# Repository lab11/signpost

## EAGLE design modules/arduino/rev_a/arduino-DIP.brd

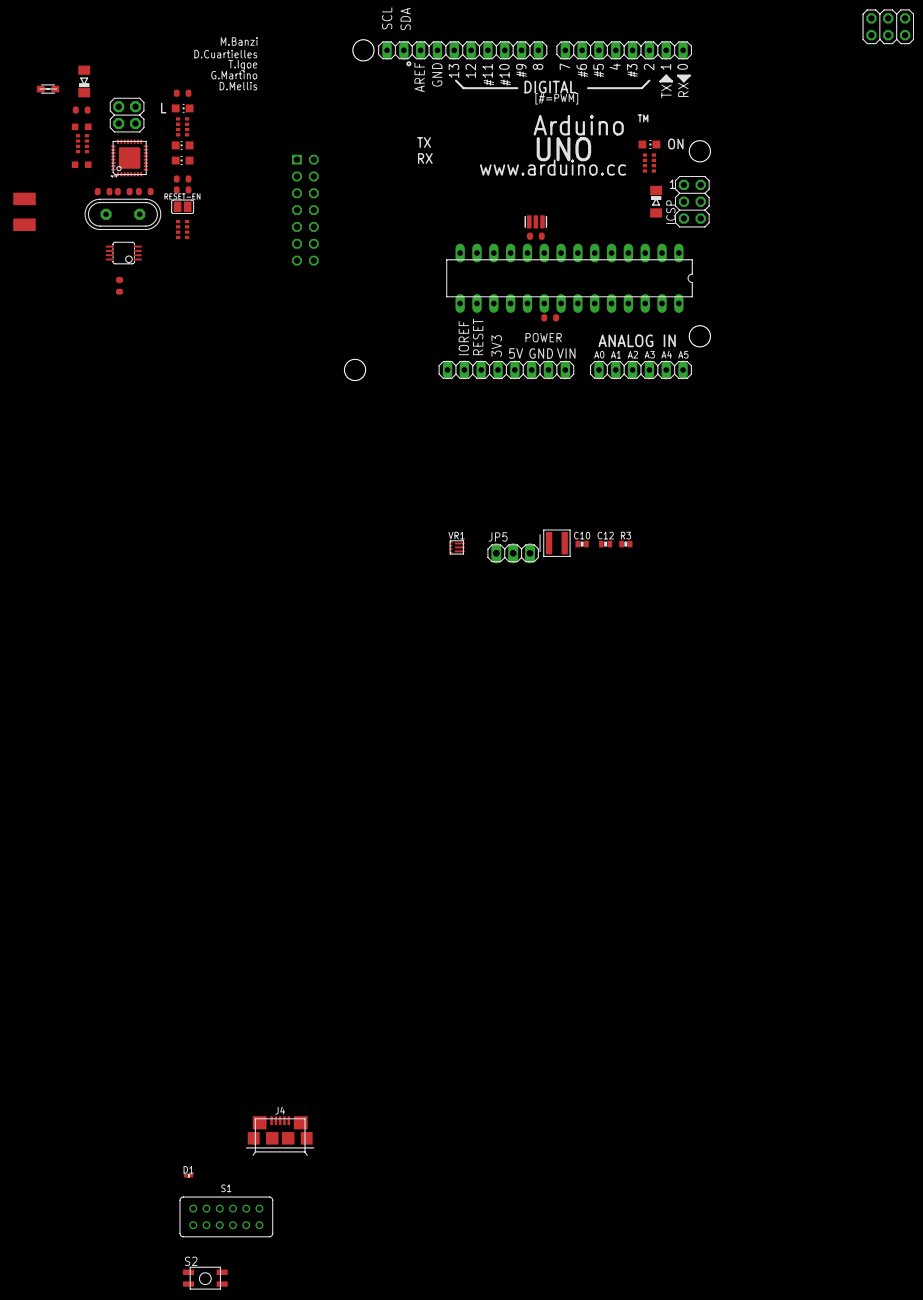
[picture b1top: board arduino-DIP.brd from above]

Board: 2 copper layers, 49 parts (1 on the bottom side), 67 nets, no tracks yet.

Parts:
AD: 6x1F-H8.5; 1X06
C1, C4, C5, C6, C7: 100n; C0603-ROUND
C8: 1u; C0603-ROUND
C9, C11: 22p; C0603-ROUND
C10: 10uF; 0603_CAP
C12: 22uF; 0603_CAP
D1: DIODE; 0402_DIODE
D2, D3: CD1206-S01575; MINIMELF
F1: MF-MSMF050-2 500mA; L1812
GROUND: SJ
ICSP, ICSP1: 3x2 M; 2X03
IOH: 10x1F-H8.5; 1X10
IOL: 8x1F-H8.5; 1X08
J1: MODULE_GENERIC
J4: MICRO_USB_B_HIROSE_ZX62-B-5PA(11); USB_MICRO_B-HIROSE-ZX62-B-5PA(11)
JP2: 2x2 M - NM; 2X02
JP5: 1X03
L: YELLOW; CHIP-LED0805
L1: BLM21; 0805
L2: 0.47uH; XFL4015
ON: GREEN; CHIP-LED0805
POWER: 8x1F-H8.5; 1X08
R1, R2: 1M; R0603-ROUND
R3: 1MΩ; 0603-RES
RESET-EN: SJ
RN1: 10K; CAY16
RN2, RN4: 1K; CAY16
RN3: 22R; CAY16
RX: YELLOW; CHIP-LED0805
S1: MFS401N-2-Z
S2: EVQP2
TX: YELLOW; CHIP-LED0805
U3: ATMEGA16U2-MU(R); MLF32
U5: LMV358IDGKR; MSOP08
VR1: TPS62086; RLT0007A
Y1: 16MHz; QS
Y2: CSTCE16M0V53-R0 16MHZ; RESONATOR
Z1, Z2: CG0603MLC-05E; CT/CN0603
ZU4: ATMEGA328P-PU; DIL28-3

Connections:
+3V3: C12.1, JP5.3, L2.2, POWER.4, R3.2, VR1.3, VR1.4
+5V: C1.2, C6.2, C7.1, D1.CATHODE, D2.C, D3.C, ICSP.2, ICSP1.2, POWER.2, POWER.5, RN1.3, RN1.5, RN2.2, RN2.3, RN4.3, RN4.4, U3.4, U3.32, U5.8, ZU4.7, ZU4.20
AD0: AD.1, ZU4.23
AD1: AD.2, ZU4.24
AD2: AD.3, ZU4.25
AD3: AD.4, ZU4.26
AD4/SDA: AD.5, IOH.9, ZU4.27
AD5/SCL: AD.6, IOH.10, ZU4.28
ARD_USB_D+: RN3.5, S1.8, Z1.1
ARD_USB_D-: RN3.8, S1.5, Z2.1
ARD_USB_GND: C8.2, GROUND.2, L1.1, S1.11, U3.28
ARD_USB_VBUS: D1.ANODE, F1.2, S1.2
AREF: C4.2, IOH.8, ZU4.21
DTR: C5.1, RN2.4, U3.13
EXT_USB_D+: J4.3, S1.9
EXT_USB_D-: J4.2, S1.6
EXT_USB_GND: J4.5, S1.12
EXT_USB_VBUS: J4.1, S1.3
GND: C1.1, C4.1, C6.1, C7.2, C9.2, C10.2, C11.2, C12.2, GROUND.1, ICSP.6, ICSP1.6, IOH.7, J1.1, J1.14, L.C, ON.C, POWER.6, POWER.7, RN2.5, S1.10, S2.P$1, S2.P$3, U3.3, U3.33, U5.4, VR1.5, Y2.2, ZU4.8, ZU4.22
IO0: IOL.1, RN4.2, ZU4.2
IO1: IOL.2, RN4.1, ZU4.3
IO2: IOL.3, ZU4.4
IO3: IOL.4, ZU4.5
IO4: IOL.5, ZU4.6
IO5: IOL.6, ZU4.11
IO6: IOL.7, ZU4.12
IO7: IOL.8, ZU4.13
IO8: IOH.1, ZU4.14
IO9: IOH.2, ZU4.15
L13: RN2.8, U5.6, U5.7
M8RXD: RN4.7, U3.9
M8TXD: RN4.8, U3.8
MISO: ICSP.1, IOH.5, ZU4.18
MISO2: ICSP1.1, U3.17
MOD_5V: C10.1, J1.2, JP5.1, VR1.1, VR1.7
MOD_USB_D+: J1.11, S1.7
MOD_USB_D-: J1.12, S1.4
MOD_USB_VBUS: J1.13, S1.1
MOD_VCCIO: J1.4, JP5.2
MOSI: ICSP.4, IOH.4, ZU4.17
MOSI2: ICSP1.4, U3.16
unnamed: L.A, RN2.1
unnamed: L2.1, VR1.6
unnamed: ON.A, RN4.5, RN4.6
unnamed: RN2.7, RX.A
unnamed: RN2.6, TX.A
PB4: JP2.1, U3.18
PB5: JP2.3, U3.19
PB6: JP2.2, U3.20
PB7: JP2.4, U3.21
POWER_GOOD: R3.1, VR1.2
RD+: RN3.4, U3.29
RD-: RN3.1, U3.30
RESET: C5.2, D2.A, ICSP.5, POWER.3, RESET-EN.1, RESET-EN.2, RN1.4, S2.P$2, S2.P$4, ZU4.1
RESET2: D3.A, ICSP1.5, RN1.6, U3.24
RXLED: RX.C, U3.10
SCK: ICSP.3, IOH.6, U5.5, ZU4.19
SCK2: ICSP1.3, U3.15
SS: IOH.3, ZU4.16
TP_VUCAP: C8.1, U3.27
TXLED: TX.C, U3.11
USBVCC: F1.1, U3.31
USHIELD: L1.2, Z1.2, Z2.2
XT1: C9.1, R1.1, U3.1, Y1.2
XT2: C11.1, R1.2, U3.2, Y1.1
XTAL1: R2.1, Y2.3, ZU4.9
XTAL2: R2.2, Y2.1, ZU4.10

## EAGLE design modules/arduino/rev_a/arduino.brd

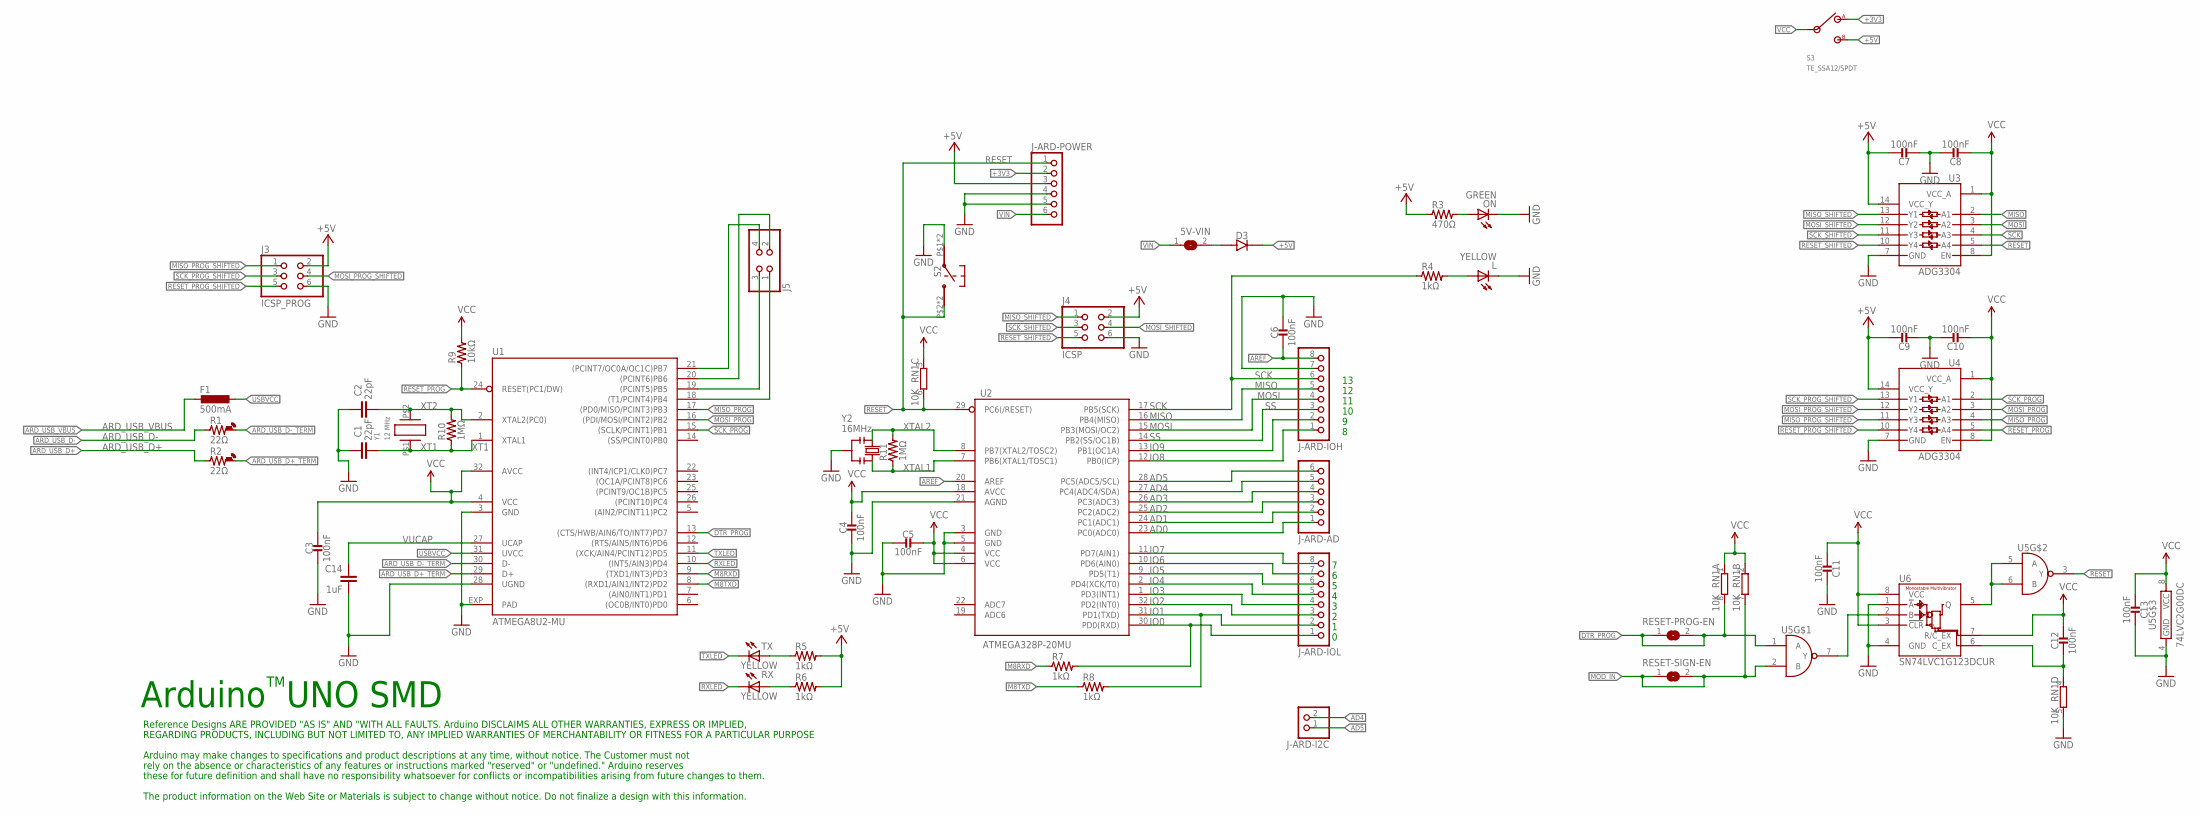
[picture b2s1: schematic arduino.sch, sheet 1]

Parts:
5V-VIN: SJ
C1, C2: 22pF; C0603-ROUND
C3, C4, C5, C6, C7, C8, C9, C10, C11, C12, C13: 100nF; 0603_CAP
C14: 1uF; C0603-ROUND
D3: DIODE; 0402_DIODE; DIGIKEY P18981CT-ND
F1: 500mA; L1812; DIGIKEY MF-MSMF050-2CT-ND
J3: ICSP_PROG; 2X03
J4: ICSP; 2X03
J5: PINHD-2X2; 2X02
J-ARD-AD: PINHD-1X6; 1X06
J-ARD-I2C: PINHD-1X2; 1X02
J-ARD-IOH: PINHD-1X8; 1X08
J-ARD-IOL: PINHD-1X8; 1X08
J-ARD-POWER: PINHD-1X6; 1X06
L: YELLOW; CHIP-LED0805
ON: GREEN; CHIP-LED0805
R1, R2: 22Ω; 0402_RES-HIGH_SPEED
R3: 470Ω; 0603-RES
R4, R5, R6, R7, R8: 1kΩ; 0603-RES
R9: 10kΩ; 0603-RES
R10, R11: 1MΩ; 0603-RES
RESET-PROG-EN: SJ
RESET-SIGN-EN: SJ
RN1: 10K; CAY16; DIGIKEY CAY16-103J4GLFCT-ND
RX: YELLOW; CHIP-LED0805
S2: EVQP2
S3: TE_SSA12/SPDT
TX: YELLOW; CHIP-LED0805
U1: ATMEGA8U2-MU; QFN32; DIGIKEY ATMEGA8U2-MURCT-ND
U2: ATMEGA328P-20MU; MLF32; DIGIKEY ATMEGA328P-MU-ND
U3, U4: ADG3304; TSSOP-14/5MM
U5: 74LVC2G00DC; VSSOP-8
U6: SN74LVC1G123DCUR; VFSOP-8
Y1: 12 MHz; ABM3; DIGIKEY 535-9103-1-ND
Y2: 16MHz; RESONATOR; DIGIKEY 490-1198-1-ND

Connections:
+3V3: J-ARD-POWER.2, S3.1 (A); also elsewhere on the board
+5V: C7.1, C9.1, D3.CATHODE, J3.2, J4.2, J-ARD-POWER.3, R3.1, R5.2, R6.2, S3.2 (B), U3.14 (VCC_Y), U4.14 (VCC_Y); also elsewhere on the board
AD0: J-ARD-AD.1, U2.23 (PC0(ADC0))
AD1: J-ARD-AD.2, U2.24 (PC1(ADC1))
AD2: J-ARD-AD.3, U2.25 (PC2(ADC2))
AD3: J-ARD-AD.4, U2.26 (PC3(ADC3))
AD4: J-ARD-AD.5, J-ARD-I2C.2, U2.27 (PC4(ADC4/SDA))
AD5: J-ARD-AD.6, J-ARD-I2C.1, U2.28 (PC5(ADC5/SCL))
ARD_USB_D+: R2.2; also elsewhere on the board
ARD_USB_D+_TERM: R2.1, U1.29 (D+)
ARD_USB_D-: R1.2; also elsewhere on the board
ARD_USB_D-_TERM: R1.1, U1.30 (D-)
ARD_USB_VBUS: F1.2; also elsewhere on the board
AREF: C6.2, J-ARD-IOH.8, U2.20 (AREF)
DTR_PROG: RESET-PROG-EN.1, RESET-PROG-EN.2, RN1.8 (2), U1.13 ((CTS/HWB/AIN6/TO/INT7)PD7), U5.1 (A)
GND: C1.2, C2.2, C3.2, C4.2, C5.2, C6.1, C7.2, C8.1, C9.2, C10.1, C11.1, C13.1, C14.2, J3.6, J4.6, J-ARD-IOH.7, J-ARD-POWER.4, J-ARD-POWER.5, L.C, ON.C, RN1.5 (2), S2.P$1, S2.P$3, U1.3 (GND), U1.28 (UGND), U1.EXP (PAD), U2.3 (GND), U2.5 (GND), U2.21 (AGND), U3.7 (GND), U4.7 (GND), U5.4 (GND), U6.1 (!A), U6.4 (GND), Y2.2; also elsewhere on the board
IO0: J-ARD-IOL.1, R7.2, U2.30 (PD0(RXD))
IO1: J-ARD-IOL.2, R8.2, U2.31 (PD1(TXD))
IO2: J-ARD-IOL.3, U2.32 (PD2(INT0))
IO3: J-ARD-IOL.4, U2.1 (PD3(INT1))
IO4: J-ARD-IOL.5, U2.2 (PD4(XCK/T0))
IO5: J-ARD-IOL.6, U2.9 (PD5(T1))
IO6: J-ARD-IOL.7, U2.10 (PD6(AIN0))
IO7: J-ARD-IOL.8, U2.11 (PD7(AIN1))
IO8: J-ARD-IOH.1, U2.12 (PB0(ICP))
IO9: J-ARD-IOH.2, U2.13 (PB1(OC1A))
M8RXD: R7.1, U1.9 ((TXD1/INT3)PD3)
M8TXD: R8.1, U1.8 ((RXD1/AIN1/INT2)PD2)
MISO: J-ARD-IOH.5, U2.16 (PB4(MISO)), U3.2 (A1)
MISO_PROG: U1.17 ((PD0/MISO/PCINT3)PB3), U4.4 (A3)
MISO_PROG_SHIFTED: J3.1, U4.11 (Y3)
MISO_SHIFTED: J4.1, U3.13 (Y1)
MOD_IN: RESET-SIGN-EN.1, RESET-SIGN-EN.2, RN1.7 (2), U5.2 (B); also elsewhere on the board
MOSI: J-ARD-IOH.4, U2.15 (PB3(MOSI/OC2)), U3.3 (A2)
MOSI_PROG: U1.16 ((PDI/MOSI/PCINT2)PB2), U4.3 (A2)
MOSI_PROG_SHIFTED: J3.4, U4.12 (Y2)
MOSI_SHIFTED: J4.4, U3.12 (Y2)
unnamed: L.A, R4.2
unnamed: J5.1, U1.18 ((T1/PCINT4)PB4)
unnamed: ON.A, R3.2
unnamed: J5.3, U1.19 ((PCINT5)PB5)
unnamed: J5.2, U1.20 ((PCINT6)PB6)
unnamed: J5.4, U1.21 ((PCINT7/OC0A/OC1C)PB7)
unnamed: C12.2, RN1.4 (1), U6.6 (C_EX)
unnamed: 5V-VIN.2, D3.ANODE
unnamed: U5.7 (Y), U6.2 (B)
unnamed: U5.5 (A), U5.6 (B), U6.5 (Q)
unnamed: R6.1, RX.A
unnamed: R5.1, TX.A
RESET: J-ARD-POWER.1, RN1.6 (2), S2.P$2, S2.P$4, U2.29 (PC6(/RESET)), U3.5 (A4), U5.3 (Y)
RESET_PROG: R9.1, U1.24 (RESET(PC1/DW)), U4.5 (A4)
RESET_PROG_SHIFTED: J3.5, U4.10 (Y4)
RESET_SHIFTED: J4.5, U3.10 (Y4)
RXLED: RX.C, U1.10 ((INT5/AIN3)PD4)
SCK: J-ARD-IOH.6, R4.1, U2.17 (PB5(SCK)), U3.4 (A3)
SCK_PROG: U1.15 ((SCLK/PCINT1)PB1), U4.2 (A1)
SCK_PROG_SHIFTED: J3.3, U4.13 (Y1)
SCK_SHIFTED: J4.3, U3.11 (Y3)
SS: J-ARD-IOH.3, U2.14 (PB2(SS/OC1B))
TXLED: TX.C, U1.11 ((XCK/AIN4/PCINT12)PD5)
USBVCC: F1.1, U1.31 (UVCC)
VCC: C3.1, C4.1, C5.1, C8.2, C10.2, C11.2, C12.1, C13.2, R9.2, RN1.1, RN1.2 (1), RN1.3 (1), S3.IN, U1.4 (VCC), U1.32 (AVCC), U2.4 (VCC), U2.6 (VCC), U2.18 (AVCC), U3.1 (VCC_A), U3.8 (EN), U4.1 (VCC_A), U4.8 (EN), U5.8 (VCC), U6.3 (!CLR), U6.7 (R/C_EX), U6.8 (VCC); also elsewhere on the board
VIN: 5V-VIN.1, J-ARD-POWER.6
VUCAP: C14.1, U1.27 (UCAP)
XT1: C1.1, R10.1, U1.1 (XTAL1), Y1.P$1 (1)
XT2: C2.1, R10.2, U1.2 (XTAL2(PC0)), Y1.P$2 (2)
XTAL1: R11.1, U2.7 (PB6(XTAL1/TOSC1)), Y2.3
XTAL2: R11.2, U2.8 (PB7(XTAL2/TOSC2)), Y2.1

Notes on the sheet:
Arduino UNO SMD
Reference Designs ARE PROVIDED "AS IS" AND "WITH ALL FAULTS. Arduino DISCLAIMS ALL OTHER WARRANTIES, EXPRESS OR IMPLIED,
Arduino may make changes to specifications and product descriptions at any time, without notice. The Customer must not
REGARDING PRODUCTS, INCLUDING BUT NOT LIMITED TO, ANY IMPLIED WARRANTIES OF MERCHANTABILITY OR FITNESS FOR A PARTICULAR PURPOSE
rely on the absence or characteristics of any features or instructions marked "reserved" or "undefined." Arduino reserves
these for future definition and shall have no responsibility whatsoever for conflicts or incompatibilities arising from future changes to them.
The product information on the Web Site or Materials is subject to change without notice. Do not finalize a design with this information.

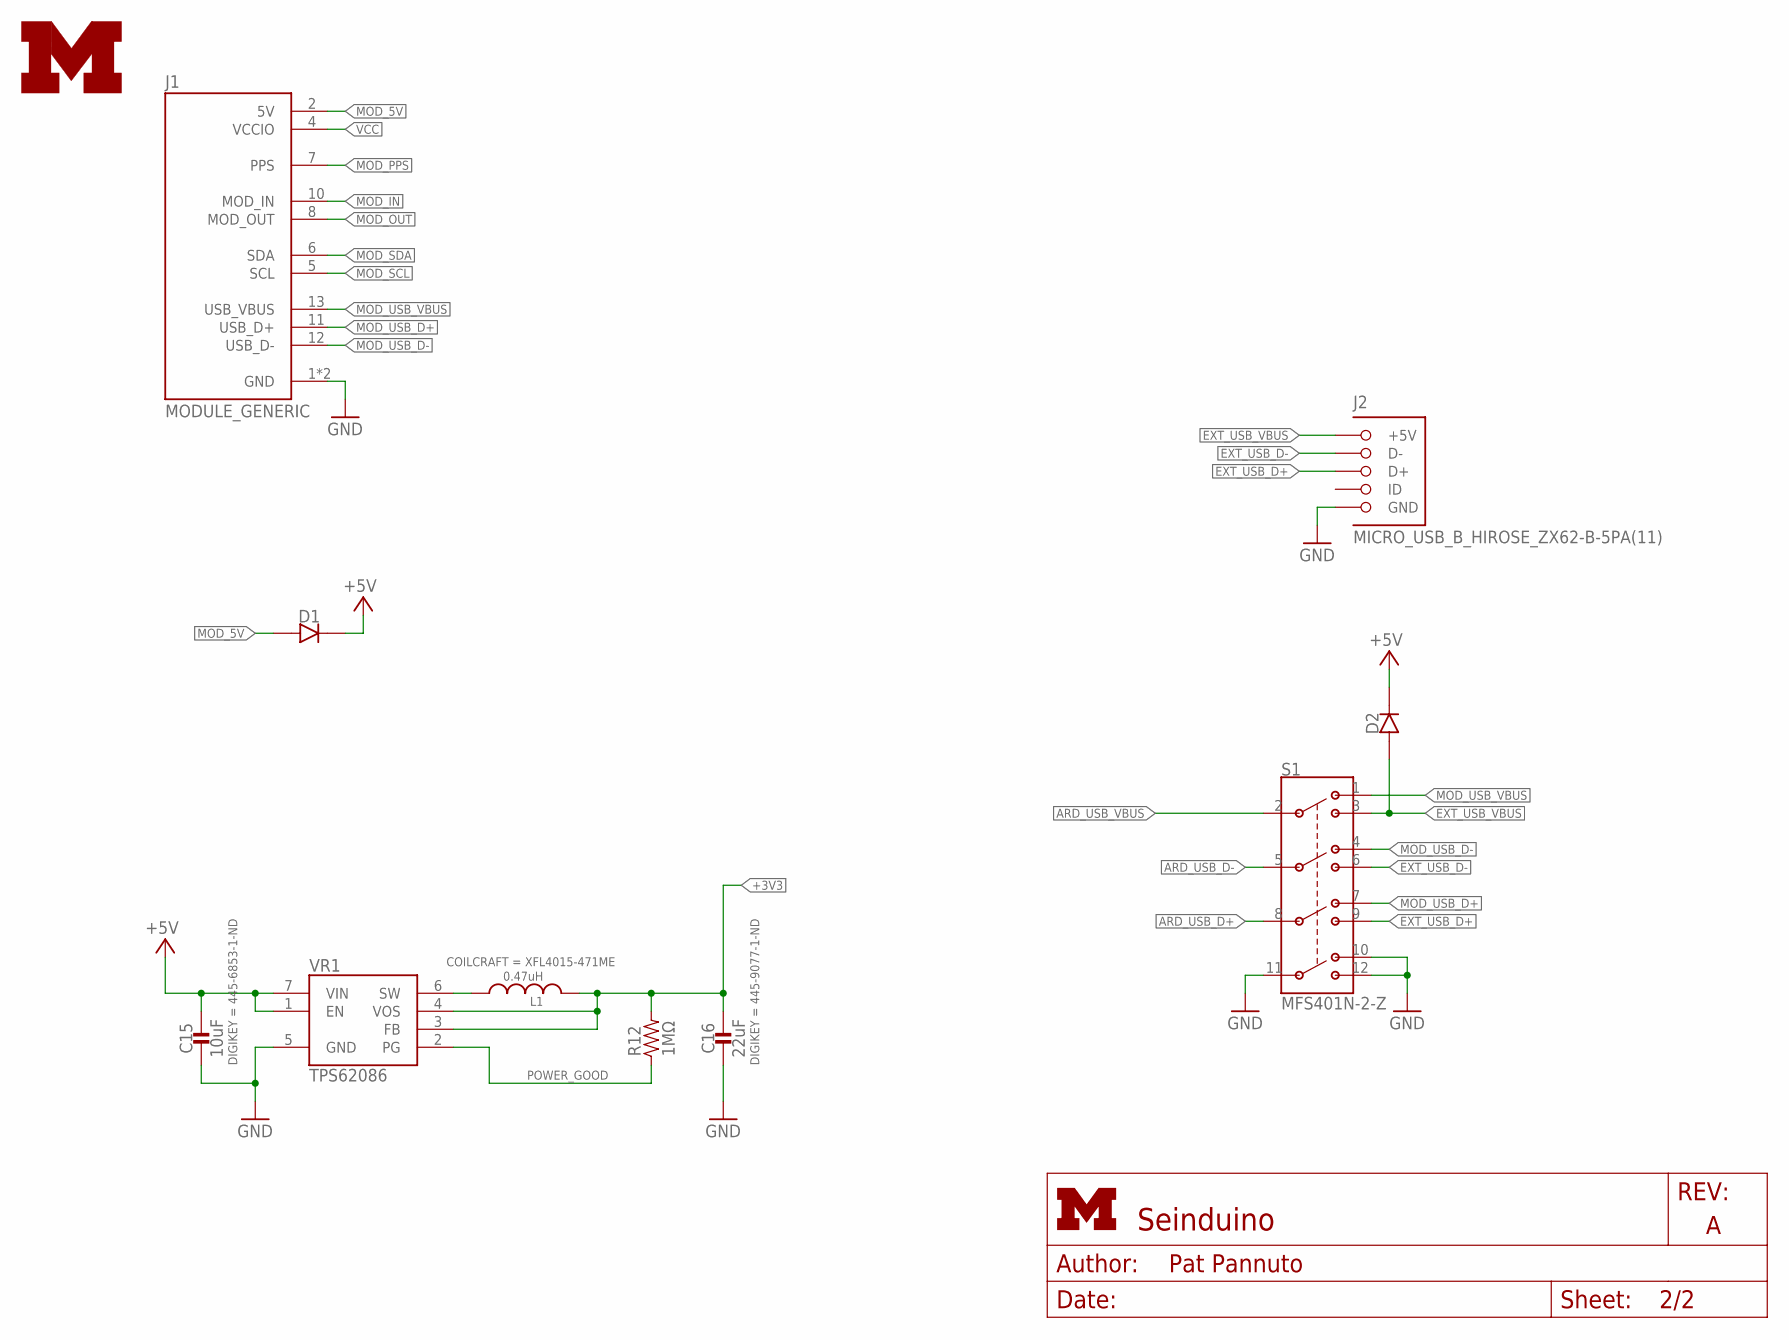
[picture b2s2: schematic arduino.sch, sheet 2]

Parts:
C15: 10uF; 0603_CAP; DIGIKEY 445-6853-1-ND
C16: 22uF; 0603_CAP; DIGIKEY 445-9077-1-ND
D1, D2: DIODE; 0402_DIODE; DIGIKEY P18981CT-ND
J1: MODULE_GENERIC
J2: MICRO_USB_B_HIROSE_ZX62-B-5PA(11); USB_MICRO_B-HIROSE-ZX62-B-5PA(11)
L1: 0.47uH; XFL4015
LOGO1: UMICH_SOLID_MEDIUM; UMICH_SOLID_200MIL
R12: 1MΩ; 0603-RES
S1: MFS401N-2-Z
VR1: TPS62086; RLT0007A

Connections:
+3V3: C16.1, L1.2, R12.2, VR1.3 (FB), VR1.4 (VOS); also elsewhere on the board
+5V: C15.1, D1.CATHODE, D2.CATHODE, VR1.1 (EN), VR1.7 (VIN); also elsewhere on the board
ARD_USB_D+: S1.8 (3P); also elsewhere on the board
ARD_USB_D-: S1.5 (2P); also elsewhere on the board
ARD_USB_VBUS: S1.2 (1P); also elsewhere on the board
EXT_USB_D+: J2.3 (D+), S1.9 (3TB)
EXT_USB_D-: J2.2 (D-), S1.6 (2TB)
EXT_USB_VBUS: D2.ANODE, J2.1 (+5V), S1.3 (1TB)
GND: C15.2, C16.2, J1.1 (GND), J1.14 (GND), J2.5 (GND), S1.10 (4TA), S1.11 (4P), S1.12 (4TB), VR1.5 (GND); also elsewhere on the board
MOD_5V: D1.ANODE, J1.2 (5V)
MOD_IN: J1.10 (MOD_IN); also elsewhere on the board
MOD_OUT: J1.8 (MOD_OUT)
MOD_PPS: J1.7 (PPS)
MOD_SCL: J1.5 (SCL)
MOD_SDA: J1.6 (SDA)
MOD_USB_D+: J1.11 (USB_D+), S1.7 (3TA)
MOD_USB_D-: J1.12 (USB_D-), S1.4 (2TA)
MOD_USB_VBUS: J1.13 (USB_VBUS), S1.1 (1TA)
POWER_GOOD: R12.1, VR1.2 (PG)
VCC: J1.4 (VCCIO); also elsewhere on the board
VR_IND_SW: L1.1, VR1.6 (SW)

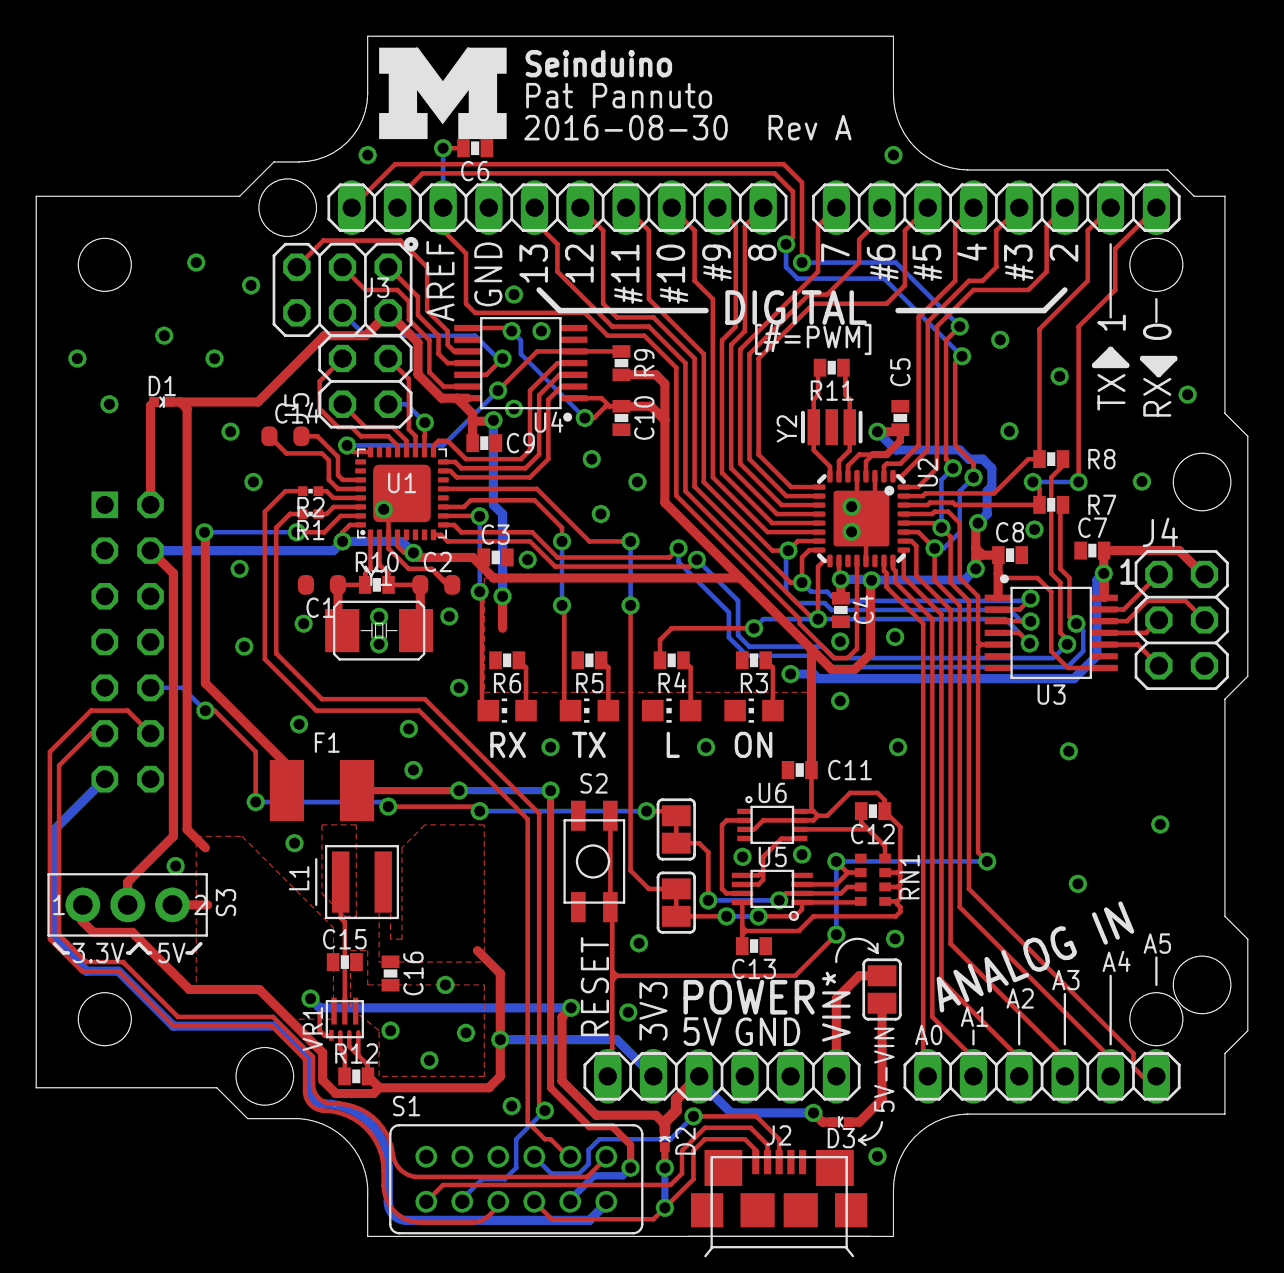
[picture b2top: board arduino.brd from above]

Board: 2 copper layers, 67.3 x 66.7 mm, 64 parts (0 on the bottom side), 77 nets.

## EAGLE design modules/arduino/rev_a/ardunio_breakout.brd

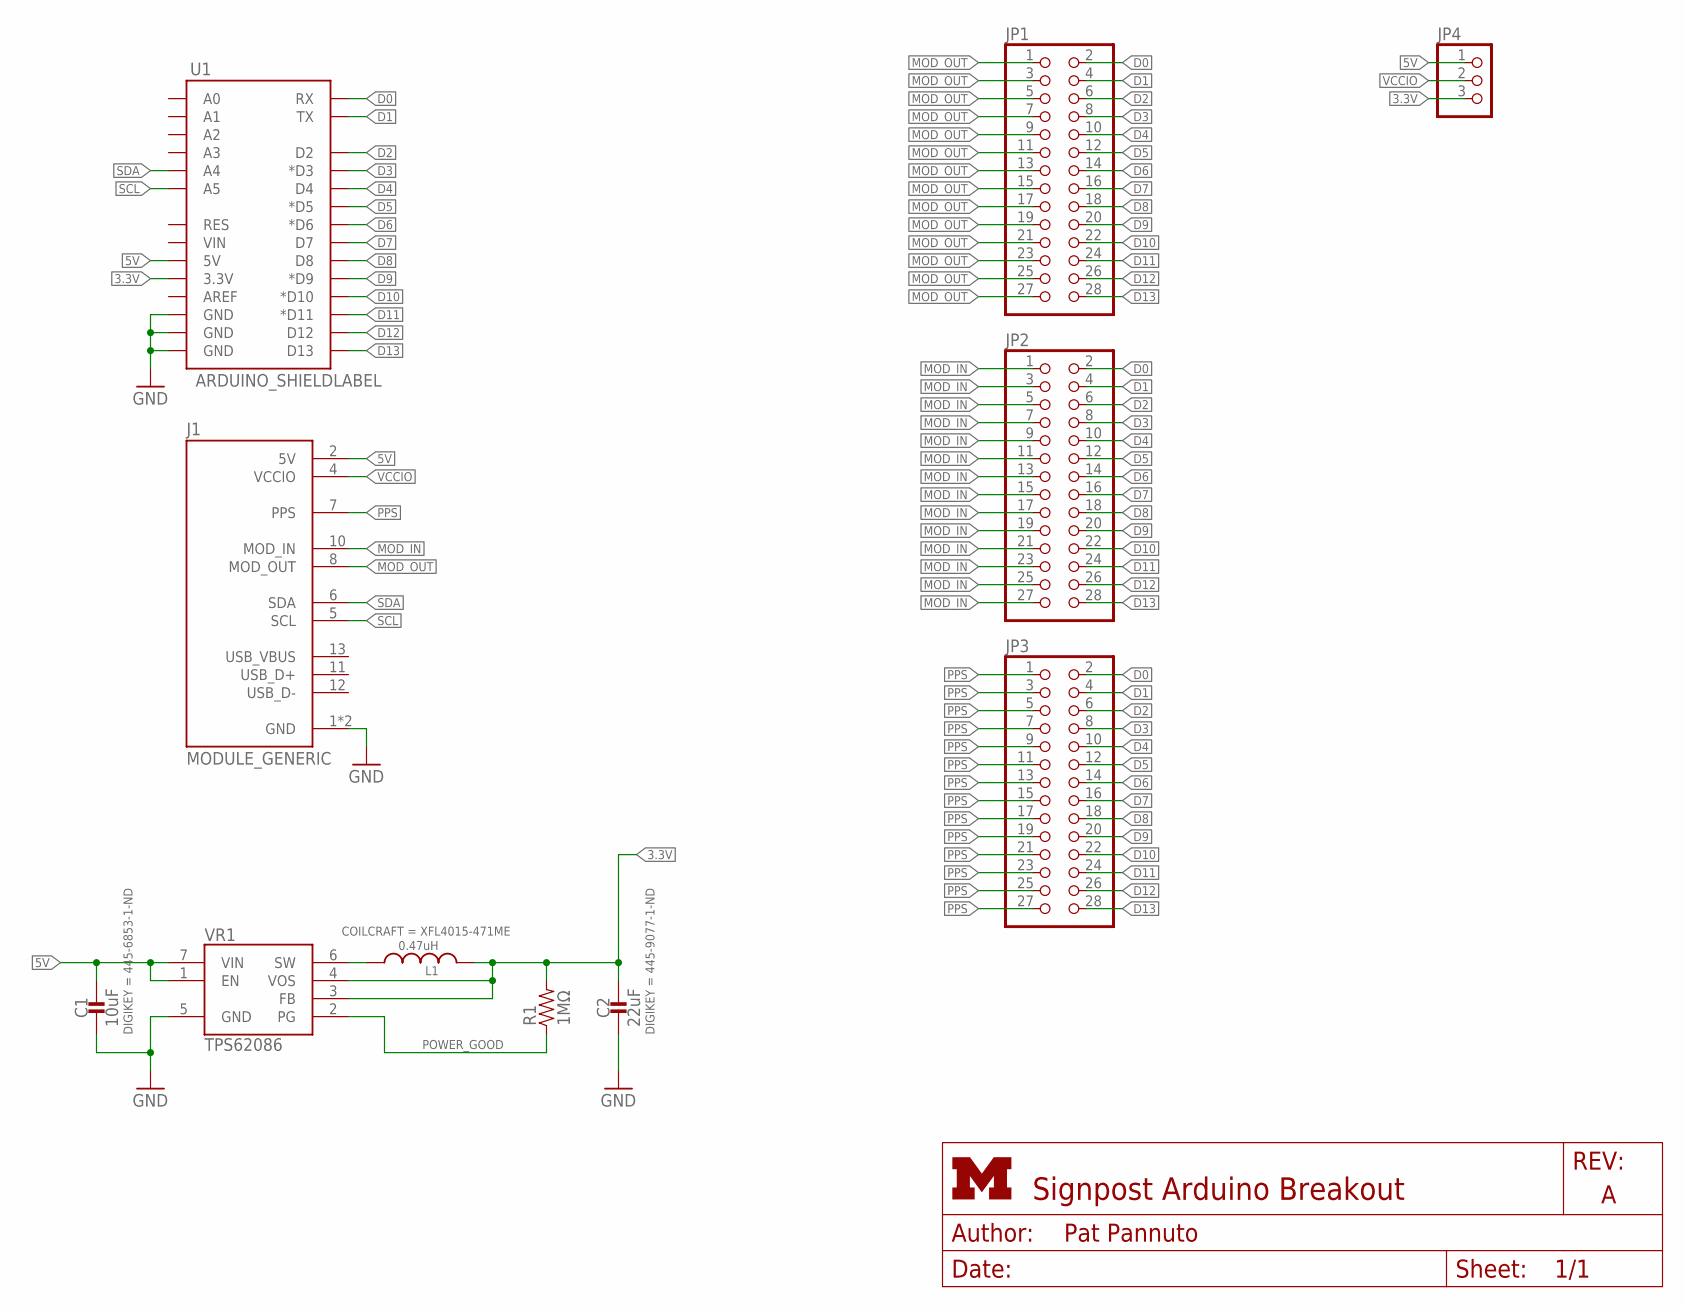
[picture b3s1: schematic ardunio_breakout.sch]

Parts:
C1: 10uF; 0603_CAP; DIGIKEY 445-6853-1-ND
C2: 22uF; 0603_CAP; DIGIKEY 445-9077-1-ND
J1: MODULE_GENERIC
JP1, JP2, JP3: PINHD-2X14; 2X14
JP4: PINHD-1X3; 1X03
L1: 0.47uH; XFL4015
R1: 1MΩ; 0603-RES
U1: ARDUINO_SHIELDLABEL; DUEMILANOVE_SHIELD
VR1: TPS62086; RLT0007A

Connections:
3.3V: C2.1, JP4.3, L1.2, R1.2, U1.3.3V, VR1.3 (FB), VR1.4 (VOS)
5V: C1.1, J1.2 (5V), JP4.1, U1.5V, VR1.1 (EN), VR1.7 (VIN)
D0: JP1.2, JP2.2, JP3.2, U1.RX
D1: JP1.4, JP2.4, JP3.4, U1.TX
D2: JP1.6, JP2.6, JP3.6, U1.D2
D3: JP1.8, JP2.8, JP3.8, U1.D3 (*D3)
D4: JP1.10, JP2.10, JP3.10, U1.D4
D5: JP1.12, JP2.12, JP3.12, U1.D5 (*D5)
D6: JP1.14, JP2.14, JP3.14, U1.D6 (*D6)
D7: JP1.16, JP2.16, JP3.16, U1.D7
D8: JP1.18, JP2.18, JP3.18, U1.D8
D9: JP1.20, JP2.20, JP3.20, U1.D9 (*D9)
D10: JP1.22, JP2.22, JP3.22, U1.D10 (*D10)
D11: JP1.24, JP2.24, JP3.24, U1.D11 (*D11)
D12: JP1.26, JP2.26, JP3.26, U1.D12
D13: JP1.28, JP2.28, JP3.28, U1.D13
GND: C1.2, C2.2, J1.1 (GND), J1.14 (GND), U1.GND@0 (GND), U1.GND@1 (GND), U1.GND@2 (GND), VR1.5 (GND)
MOD_IN: J1.10 (MOD_IN), JP2.1
MOD_OUT: J1.8 (MOD_OUT), JP1.1, JP1.3, JP1.5, JP1.7, JP1.9, JP1.11, JP1.13, JP1.15, JP1.17, JP1.19, JP1.21, JP1.23, JP1.25, JP1.27
unnamed: L1.1, VR1.6 (SW)
POWER_GOOD: R1.1, VR1.2 (PG)
PPS: J1.7 (PPS), JP3.1
SCL: J1.5 (SCL), U1.A5
SDA: J1.6 (SDA), U1.A4
VCCIO: J1.4 (VCCIO), JP4.2

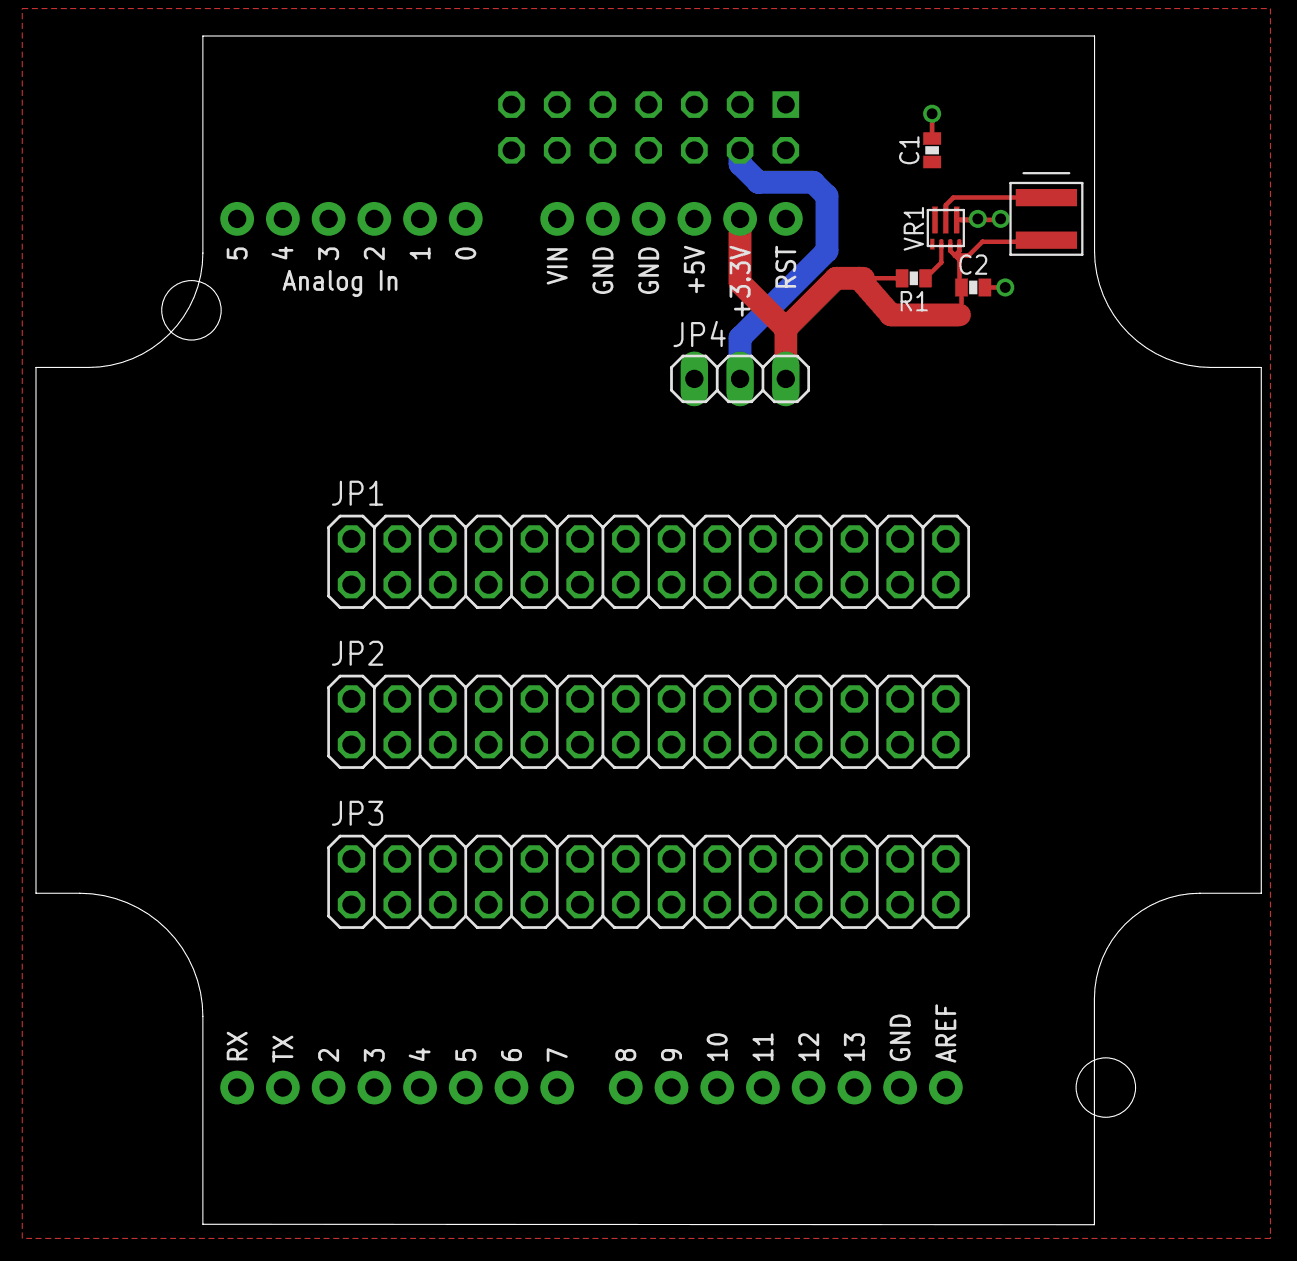
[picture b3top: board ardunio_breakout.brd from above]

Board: 2 copper layers, 68.1 x 66.0 mm, 11 parts (0 on the bottom side), 25 nets.

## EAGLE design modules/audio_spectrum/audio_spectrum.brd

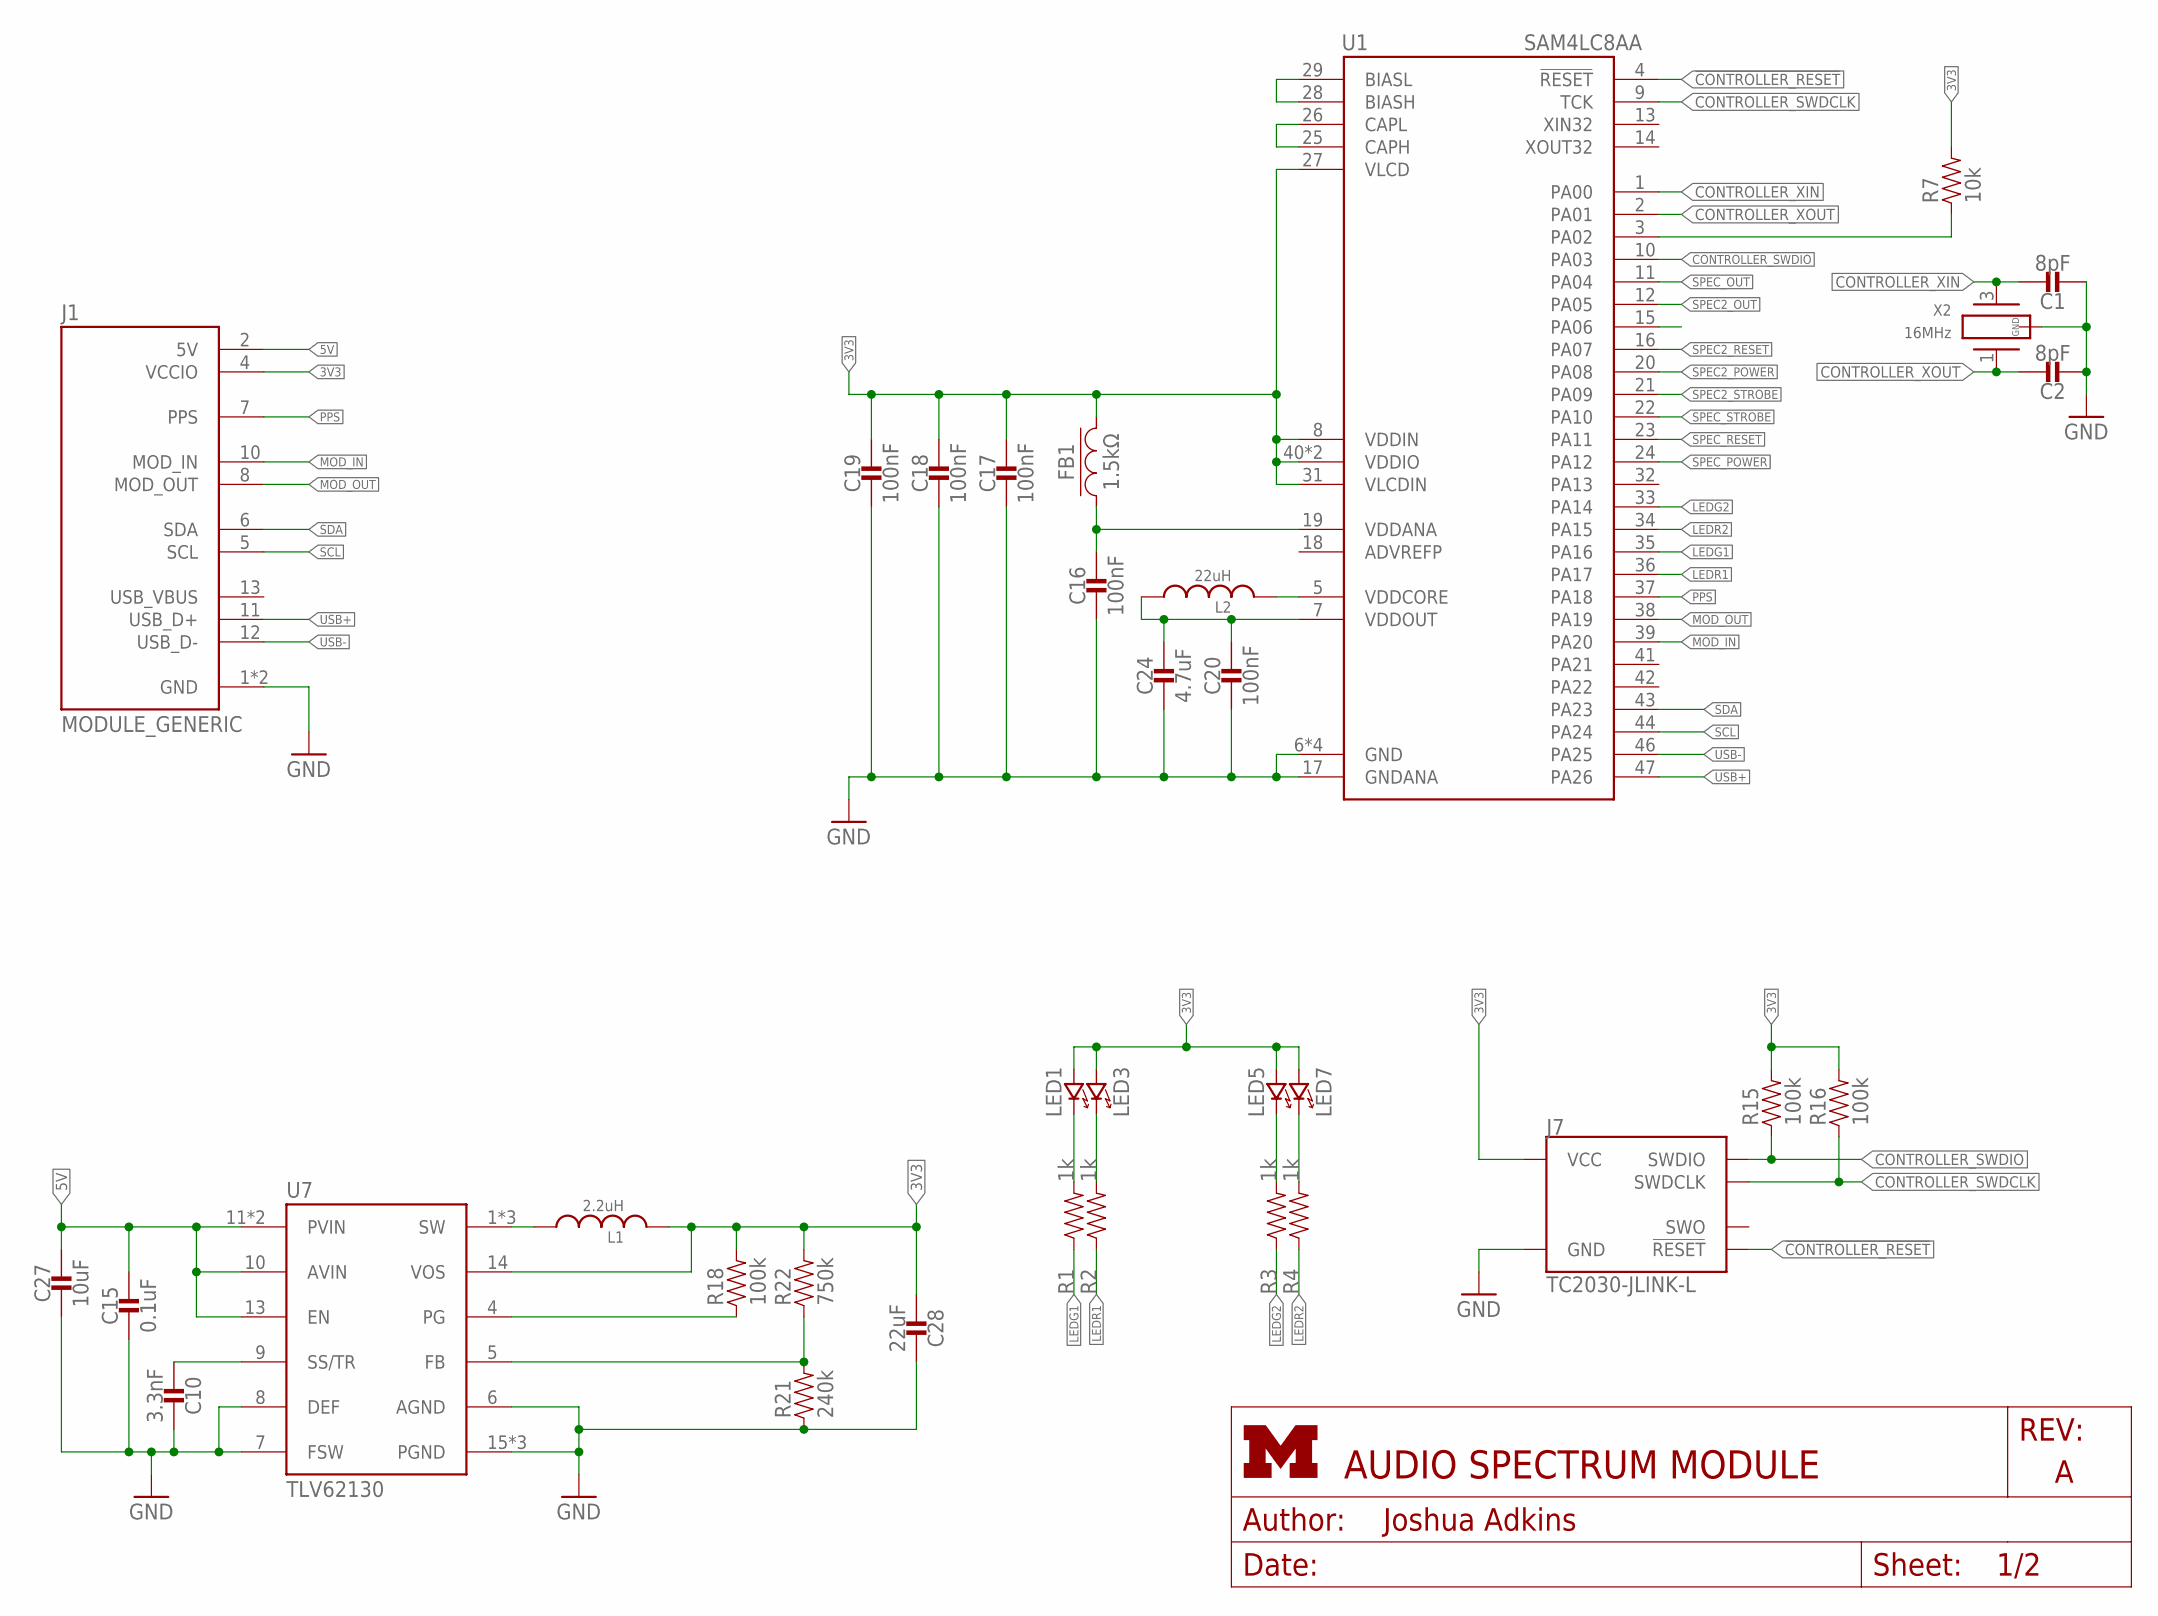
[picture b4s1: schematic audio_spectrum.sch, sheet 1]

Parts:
C1, C2: 8pF; 0603_CAP; DIGIKEY 490-8230-1-ND
C10: 3.3nF; 0603_CAP
C15: 0.1uF; 0603_CAP
C16, C17, C18, C19, C20: 100nF; 0603_CAP; DIGIKEY 490-10777-1-ND
C24: 4.7uF; 0603_CAP; DIGIKEY 490-13252-1-ND
C27: 10uF; 0603_CAP
C28: 22uF; 0603_CAP
FB1: 1.5kΩ; 0603_CAP; DIGIKEY 490-5216-1-ND
J1: MODULE_GENERIC
J7: TC2030-JLINK-L; TC2030-IDC
L1: 2.2uH; IHL-1212BZ-11
L2: 22uH; 1212
LED1, LED3, LED5, LED7: LED0603; LED-0603
R1, R2, R3, R4: 1k; 0603-RES; DIGIKEY 1276-3431-1-ND
R7: 10k; 0603-RES; DIGIKEY 1276-3431-1-ND
R15, R16: 100k; 0603-RES; DIGIKEY 1276-3432-1-ND
R18: 100k; 0603-RES
R21: 240k; 0603-RES
R22: 750k; 0603-RES
U1: SAM4LC8AA; QFN-48-7MM
U7: TLV62130; TQFN-16/3MM
X2: 16MHz; FHXXX

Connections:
3V3: C17.1, C18.1, C19.1, C28.2, FB1.2, J1.4 (VCCIO), J7.1 (VCC), L1.P$2 (2), LED1.A (ANODE), LED3.A (ANODE), LED5.A (ANODE), LED7.A (ANODE), R7.2, R15.2, R16.2, R18.2, R22.2, U1.8 (VDDIN), U1.27 (VLCD), U1.31 (VLCDIN), U1.40 (VDDIO), U1.45 (VDDIO), U7.14 (VOS); also elsewhere on the board
3VSWOUT: L1.P$1 (1), U7.1 (SW), U7.2 (SW), U7.3 (SW)
5V: C15.1, C27.1, J1.2 (5V), U7.10 (AVIN), U7.11 (PVIN), U7.12 (PVIN), U7.13 (EN)
!CONTROLLER_RESET: J7.3 (!RESET), U1.4 (!RESET)
CONTROLLER_BUCK/LDO_N: R7.1, U1.3 (PA02)
CONTROLLER_SWDCLK: J7.4 (SWDCLK), R16.1, U1.9 (TCK)
CONTROLLER_SWDIO: J7.2 (SWDIO), R15.1, U1.10 (PA03)
CONTROLLER_XIN: C1.1, U1.1 (PA00), X2.3 (2)
CONTROLLER_XOUT: C2.1, U1.2 (PA01), X2.1
GND: C1.2, C2.2, C10.1, C15.2, C16.2, C17.2, C18.2, C19.2, C20.2, C24.2, C27.2, C28.1, J1.1 (GND), J1.14 (GND), J7.5 (GND), R21.1, U1.6 (GND), U1.17 (GNDANA), U1.30 (GND), U1.48 (GND), U1.THERMAL (GND), U7.6 (AGND), U7.7 (FSW), U7.8 (DEF), U7.15 (PGND), U7.16 (PGND), U7.GND, X2.2 (GND), X2.4 (GND); also elsewhere on the board
LEDG1: R1.1, U1.35 (PA16)
LEDG2: R3.1, U1.33 (PA14)
LEDR1: R2.1, U1.36 (PA17)
LEDR2: R4.1, U1.34 (PA15)
MOD_IN: J1.10 (MOD_IN), U1.39 (PA20)
MOD_OUT: J1.8 (MOD_OUT), U1.38 (PA19)
unnamed: LED1.C (CATHODE), R1.2
unnamed: LED3.C (CATHODE), R2.2
unnamed: LED7.C (CATHODE), R4.2
unnamed: C16.1, FB1.1, U1.19 (VDDANA)
unnamed: LED5.C (CATHODE), R3.2
unnamed: C10.2, U7.9 (SS/TR)
unnamed: R18.1, U7.4 (PG)
unnamed: R21.2, R22.1, U7.5 (FB)
unnamed: C20.1, C24.1, L2.P$1 (1), U1.7 (VDDOUT)
unnamed: L2.P$2 (2), U1.5 (VDDCORE)
unnamed: U1.28 (BIASH), U1.29 (BIASL)
unnamed: U1.25 (CAPH), U1.26 (CAPL)
PPS: J1.7 (PPS), U1.37 (PA18)
SCL: J1.5 (SCL), U1.44 (PA24)
SDA: J1.6 (SDA), U1.43 (PA23)
SPEC2_OUT: U1.12 (PA05); also elsewhere on the board
SPEC2_POWER: U1.20 (PA08); also elsewhere on the board
SPEC2_RESET: U1.16 (PA07); also elsewhere on the board
SPEC2_STROBE: U1.21 (PA09); also elsewhere on the board
SPEC_OUT: U1.11 (PA04); also elsewhere on the board
SPEC_POWER: U1.24 (PA12); also elsewhere on the board
SPEC_RESET: U1.23 (PA11); also elsewhere on the board
SPEC_STROBE: U1.22 (PA10); also elsewhere on the board
USB+: J1.11 (USB_D+), U1.47 (PA26)
USB-: J1.12 (USB_D-), U1.46 (PA25)

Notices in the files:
parts and their libraries:
SparkFun-Aesthetics: Licensing: CC v3.0 Share-Alike You are welcome to use this library for commercial purposes.
